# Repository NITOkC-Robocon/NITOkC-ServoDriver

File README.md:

# NITOkC-ServoDriver

## 概要
弊部独自のサーボドライバの回路データ、およびプログラムです<br>
(※デフォルトブランチ：main)

## 機能
- 2セルLiPoバッテリーからの給電
  - マイコンへの給電(電源切り離し機能付き)
  - サーボへの給電(レギュレータにより6Vに降圧)
- 中点指定機能
- 出力選択機能
- PWM幅可変機能
- 外部入力機能
  - 基板上のスライドスイッチによって切り替え可能

## 環境
|          |     |
|   :-:    | --- |
| OS       | Windows 10 Pro |
| プログラム | Arm Keil Studio |
| 基板作成 | KiCad 7.0 |
| 使用マイコン | NUCLEO-F303K8 |
| 使用言語    | C++ |
| その他   | 弊部独自ライブラリの導入が必須(Privateリポジトリのため、今後依存関係を解消予定) |

## 開発者
[Resenaga_Byakko (Shogo Miyazato)](https://github.com/ByakkoMatsumiya)

## 連絡先
基板またはコードに関するお問い合わせは、[Issues](https://github.com/NITOkC-Robocon/NITOC-Robocon_HP/issues)または下記連絡先へお願い致します。
- [Twitter | @Seyanaga (趣味用アカウント)](https://twitter.com/Seyanaga)
- [Twitter | @Myaaaazato (ロボコン用アカウント)](https://twitter.com/Myaaaazato)

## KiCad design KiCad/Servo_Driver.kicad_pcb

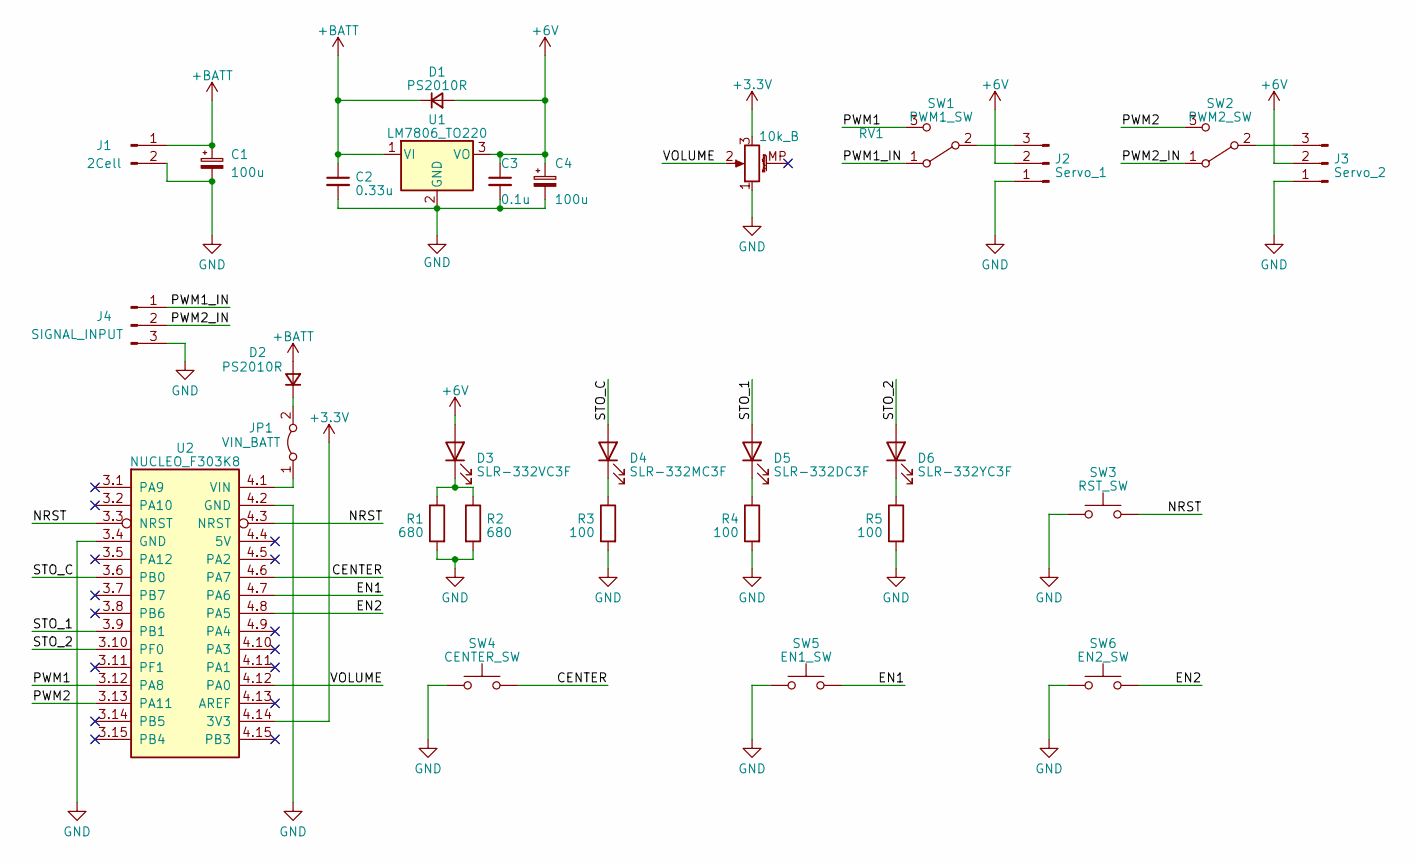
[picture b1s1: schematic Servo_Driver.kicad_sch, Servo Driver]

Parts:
C1, C4: 100u; CP_Radial_D8.0mm_P3.50mm
C2: 0.33u; C_Disc_D3.4mm_W2.1mm_P2.50mm
C3: 0.1u; C_Disc_D4.3mm_W1.9mm_P5.00mm
D1, D2: PS2010R; D_DO-15_P10.16mm_Horizontal
D3: SLR-332VC3F; LED_D3.0mm
D4: SLR-332MC3F; LED_D3.0mm
D5: SLR-332DC3F; LED_D3.0mm
D6: SLR-332YC3F; LED_D3.0mm
J1: 2Cell; Connector_T_Male
J2: Servo_1; PinHeader_1x03_P2.54mm_Vertical
J3: Servo_2; PinHeader_1x03_P2.54mm_Vertical
J4: SIGNAL_INPUT; PinHeader_1x03_P2.54mm_Vertical
JP1: VIN_BATT; PinHeader_1x02_P2.54mm_Vertical
R1, R2: 680; R_Axial_DIN0207_L6.3mm_D2.5mm_P10.16mm_Horizontal
R3, R4, R5: 100; R_Axial_DIN0207_L6.3mm_D2.5mm_P10.16mm_Horizontal
RV1: 10k_B; Potentiometer_Alps_RK09K_Single_Vertical
SW1: PWM1_SW; Slide_SS12D01Gx
SW2: PWM2_SW; Slide_SS12D01Gx
SW3: RST_SW; SW_PUSH_6mm
SW4: CENTER_SW; SW_PUSH_6mm
SW5: EN1_SW; SW_PUSH_6mm
SW6: EN2_SW; SW_PUSH_6mm
U1: LM7806_TO220; TO-220-3_Vertical
U2: NUCLEO_F303K8; NUCLEO F303 K8

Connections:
+3.3V: RV1.3, U2.4.14 (3V3)
+6V: C3.1, C4.1, D1.2 (A), D3.2 (A), J2.2, J3.2, U1.3 (VO)
+BATT: C1.1, C2.1, D1.1 (K), D2.2 (A), J1.1, U1.1 (VI)
/CENTER: SW4.2, U2.4.6 (PA7)
/EN1: SW5.2, U2.4.7 (PA6)
/EN2: SW6.2, U2.4.8 (PA5)
/NRST: SW3.2, U2.3.3 (NRST), U2.4.3 (NRST)
/PWM1: SW1.3 (C), U2.3.12 (PA8)
/PWM1_IN: J4.1, SW1.1 (A)
/PWM2: SW2.3 (C), U2.3.13 (PA11~)
/PWM2_IN: J4.2, SW2.1 (A)
/STO_1: D5.2 (A), U2.3.9 (PB1)
/STO_2: D6.2 (A), U2.3.10 (PF0)
/STO_C: D4.2 (A), U2.3.6 (PB0)
/VOLUME: RV1.2, U2.4.12 (PA0)
GND: C1.2, C2.2, C3.2, C4.2, J1.2, J2.1, J3.1, J4.3, R1.2, R2.2, R3.2, R4.2, R5.2, RV1.1, SW3.1, SW4.1, SW5.1, SW6.1, U1.2 (GND), U2.3.4 (GND), U2.4.2 (GND)
unnamed: D2.1 (K), JP1.2 (B)
unnamed: D3.1 (K), R1.1, R2.1
unnamed: D4.1 (K), R3.1
unnamed: D5.1 (K), R4.1
unnamed: D6.1 (K), R5.1
unnamed: J2.3, SW1.2 (B)
unnamed: J3.3, SW2.2 (B)
unnamed: JP1.1 (A), U2.4.1 (VIN)

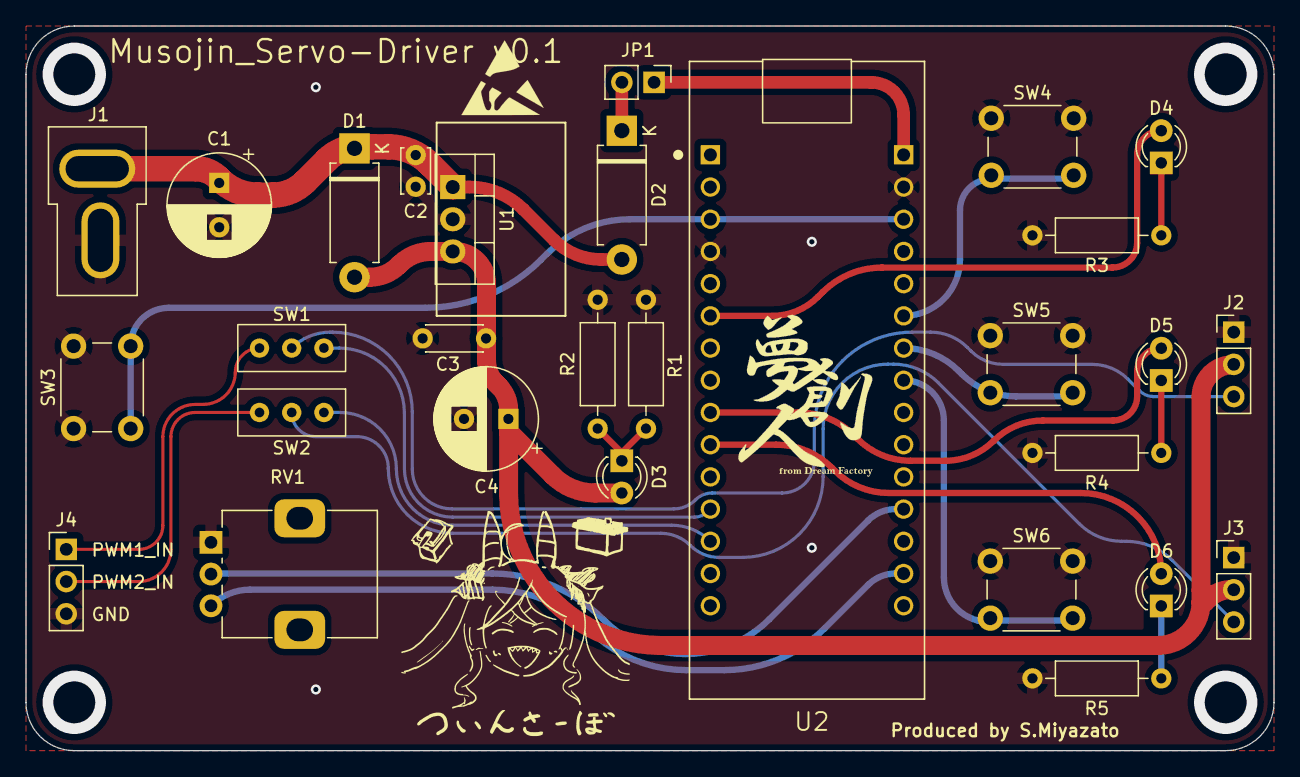
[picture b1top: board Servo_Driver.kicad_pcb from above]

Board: 2 copper layers, 98.4 x 57.2 mm, 29 parts (0 on the bottom side), 24 nets.

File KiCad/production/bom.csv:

Designator,Footprint,Quantity,Value,LCSC Part #
"C1, C4",CP_Radial_D8.0mm_P3.50mm,2,100u,
C2,C_Disc_D3.4mm_W2.1mm_P2.50mm,1,0.33u,
C3,C_Disc_D4.3mm_W1.9mm_P5.00mm,1,0.1u,
"D1, D2",D_DO-15_P10.16mm_Horizontal,2,PS2010R,
D3,LED_D3.0mm,1,SLR-332VC3F,
D4,LED_D3.0mm,1,SLR-332MC3F,
D5,LED_D3.0mm,1,SLR-332DC3F,
D6,LED_D3.0mm,1,SLR-332YC3F,
J1,Connector_T_Male,1,2Cell,
J2,PinHeader_1x03_P2.54mm_Vertical,1,Servo_1,
J3,PinHeader_1x03_P2.54mm_Vertical,1,Servo_2,
J4,PinHeader_1x03_P2.54mm_Vertical,1,SIGNAL_INPUT,
JP1,PinHeader_1x02_P2.54mm_Vertical,1,VIN_BATT,
"R1, R2",R_Axial_DIN0207_L6.3mm_D2.5mm_P10.16mm_Horizontal,2,680,
"R3, R4, R5",R_Axial_DIN0207_L6.3mm_D2.5mm_P10.16mm_Horizontal,3,100,
RV1,Potentiometer_Alps_RK09K_Single_Vertical,1,10k_B,
SW1,Slide_SS12D01Gx,1,PWM1_SW,
SW2,Slide_SS12D01Gx,1,PWM2_SW,
SW3,SW_PUSH_6mm,1,RST_SW,
SW4,SW_PUSH_6mm,1,CENTER_SW,
SW5,SW_PUSH_6mm,1,EN1_SW,
SW6,SW_PUSH_6mm,1,EN2_SW,
U1,TO-220-3_Vertical,1,LM7806_TO220,
U2,NUCLEO F303 K8,1,NUCLEO_F303K8,

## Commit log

2023-06-28 Upload kicad files.
2023-06-28 Change directory composition.
2023-06-28 Add a source code.
2023-06-28 ピン配置と関数分けを実施
2023-06-29 可変PWM幅制御の実装、LED点灯用の関数を追記
2023-06-29 出力切替機能の実装、中点SW押下時の挙動の修正
2023-07-07 基板を更新。部品配置の変更とフットプリントの配置
2023-07-17 実機での動作確認に伴い不具合を修正
2023-07-17 基板にシルクスクリーンを追加、その他位置を微調整
